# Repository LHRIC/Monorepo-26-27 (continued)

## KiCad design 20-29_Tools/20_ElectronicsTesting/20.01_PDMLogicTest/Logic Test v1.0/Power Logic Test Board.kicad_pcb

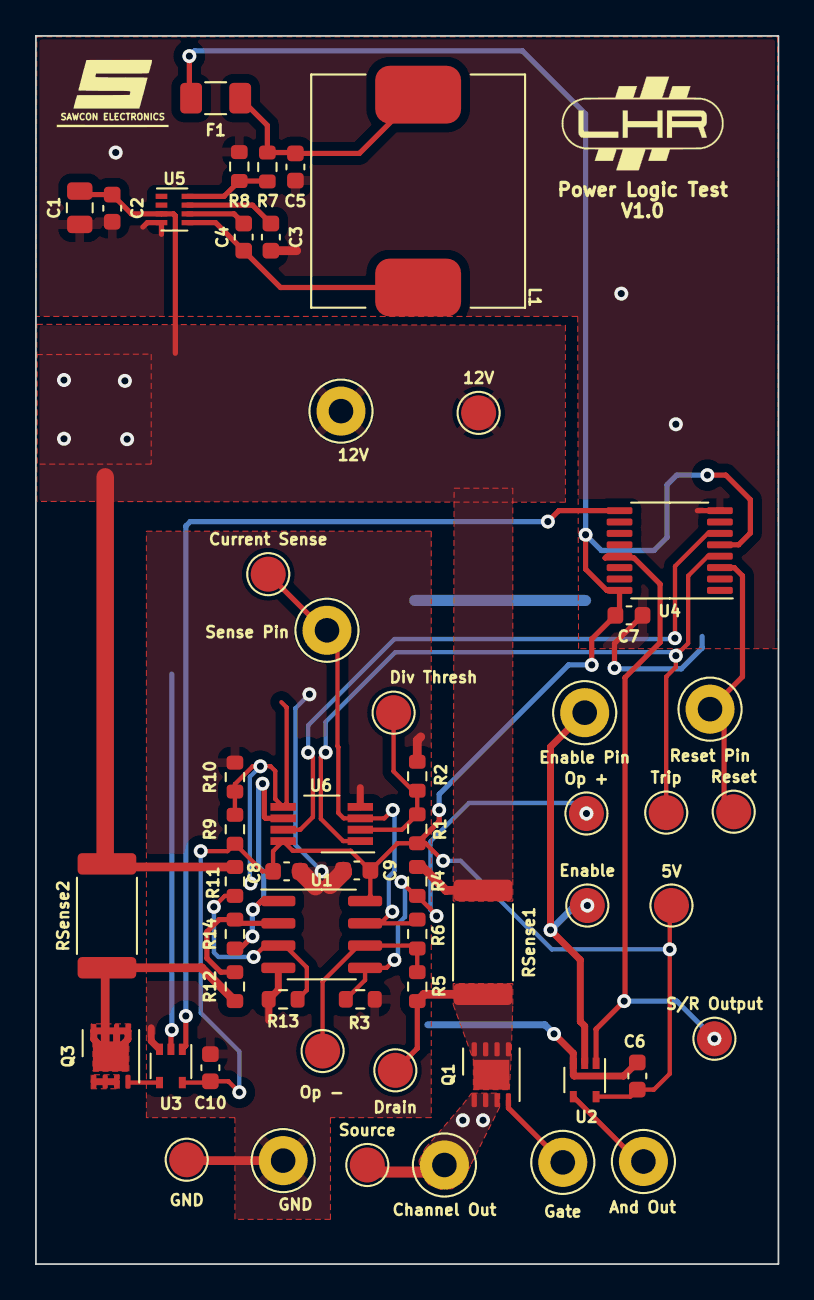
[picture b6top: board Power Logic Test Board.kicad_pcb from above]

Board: 2 copper layers, 42.3 x 70.0 mm, 57 parts (0 on the bottom side), 29 nets.

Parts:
5V, 12V: TP; TestPoint_Pad_D2.0mm
12V#2: TestPoint; TestPoint_Loop_D3.50mm_Drill1.4mm_Beaded
And Out: TestPoint; TestPoint_Loop_D3.50mm_Drill1.4mm_Beaded
C1: 10uF; C_0805_2012Metric
C2, C4: 0.1uF; C_0603_1608Metric
C3: 33nF; C_0603_1608Metric
C5: 47uF; C_0603_1608Metric
C6, C7, C8, C9, C10: C_Small; C_0603_1608Metric
Channel Out: TestPoint; TestPoint_Loop_D3.50mm_Drill1.4mm_Beaded
Current Sense: TestPoint; TestPoint_Pad_D2.0mm
Div Thresh: TestPoint; TestPoint_Pad_D2.0mm
Drain: TestPoint; TestPoint_Pad_D2.0mm
Enable: TestPoint; TestPoint_Pad_D2.0mm
Enable Pin: TestPoint; TestPoint_Loop_D3.50mm_Drill1.4mm_Beaded
F1: 750mA; Fuse_1206_3216Metric
GND: TestPoint; TestPoint_Loop_D3.50mm_Drill1.4mm_Beaded
GND#2: TestPoint; TestPoint_Pad_D2.0mm
Gate: TestPoint; TestPoint_Loop_D3.50mm_Drill1.4mm_Beaded
L1: 5.6uH; HCMA1305-5R6-R
Op +: TestPoint; TestPoint_Pad_D2.0mm
Op -: TestPoint; TestPoint_Pad_D2.0mm
Q1, Q3: NMOS; DFN-8-1EP_3x3mm_P0.65mm_EP1.7x2.05mm
R1, R2, R3, R4, R5, R6, R9, R10, R11, R12, R13, R14: R_Small; R_0603_1608Metric
R7: 52.3k; R_0603_1608Metric
R8: 10k; R_0603_1608Metric
RSense1, RSense2: R_Small; R_2512_6332Metric
Reset: TestPoint; TestPoint_Pad_D2.0mm
Reset Pin: TestPoint; TestPoint_Loop_D3.50mm_Drill1.4mm_Beaded
S/R Output: TestPoint; TestPoint_Pad_D2.0mm
Sense Pin: TestPoint; TestPoint_Loop_D3.50mm_Drill1.4mm_Beaded
Source: TestPoint; TestPoint_Pad_D2.0mm
Trip: TestPoint; TestPoint_Pad_D2.0mm
U1: Opamp_Dual; SOIC-8_3.9x4.9mm_P1.27mm
U2, U3: 74AHC1G08; SOT-353_SC-70-5
U4: CD4044B; TSSOP-16_4.4x5mm_P0.65mm
U5: TPS62933; SOT-583
U6: TLV7012DGKR; VSSOP-8_3.0x3.0mm_P0.65mm

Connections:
+5V: 5V.1, C6.1, C7.1, C8.1, C9.1, C10.1, F1.2, R1.1, R9.1, U1.8 (V+), U2.5 (VCC), U3.5 (VCC), U4.5 (Enable), U4.16 (V+), U6.8 (V+)
+12V: 12V.1, 12V#2.1, C1.1, C2.1, R4.1, R11.1, RSense1.1, RSense2.1, U5.3 (VIN)
/Current Sense: R14.1, U1.1, U6.6 (-)
/Drain: Drain.1, Q1.5 (D), Q1.6 (D), Q1.7 (D), Q1.8 (D), Q1.9 (D), R5.1, RSense1.2
/Fault: U3.1, U4.9 (Q)
/Gate: Gate.1, Q1.4 (G)
/Load+: Q3.1 (S), Q3.2 (S), Q3.3 (S)
/Source: Channel Out.1, Q1.1 (S), Q1.2 (S), Q1.3 (S), Source.1
GND: C1.2, C2.2, C3.2, C5.2, C6.2, C7.2, C8.2, C9.2, C10.2, GND.1, GND#2.1, R2.2, R3.2, R8.2, R10.2, R13.2, U1.4 (V-), U2.3 (GND), U3.3 (GND), U4.8 (V-), U5.4 (GND), U6.4 (V-)
unnamed: C5.1, F1.1, L1.2, R7.1
unnamed: Q3.5 (D), Q3.6 (D), Q3.7 (D), Q3.8 (D), Q3.9 (D), R12.1, RSense2.2
unnamed: Q3.4 (G), U3.4
unnamed: Enable.1, Enable Pin.1, U2.2
unnamed: And Out.1, U2.4
unnamed: R11.2, R13.1, U1.3 (+)
unnamed: R12.2, R14.2, U1.2 (-)
unnamed: Op +.1, R3.1, R4.2, U1.5 (+)
unnamed: Op -.1, R5.2, R6.1, U1.6 (-)
unnamed: S/R Output.1, U2.1, U4.13 (Q)
unnamed: Trip.1, U4.4 (R), U6.1
unnamed: Reset.1, Reset Pin.1, U4.3 (S)
unnamed: U4.6 (R), U6.7
unnamed: C4.1, U5.6 (BST)
unnamed: R7.2, R8.1, U5.8 (FB)
unnamed: C3.1, U5.7 (SS)
unnamed: C4.2, L1.1, U5.5 (SW)
unnamed: Current Sense.1, R6.2, Sense Pin.1, U1.7, U6.3 (+)
unnamed: Div Thresh.1, R1.2, R2.1, U6.2 (-)
unnamed: R9.2, R10.1, U6.5 (+)

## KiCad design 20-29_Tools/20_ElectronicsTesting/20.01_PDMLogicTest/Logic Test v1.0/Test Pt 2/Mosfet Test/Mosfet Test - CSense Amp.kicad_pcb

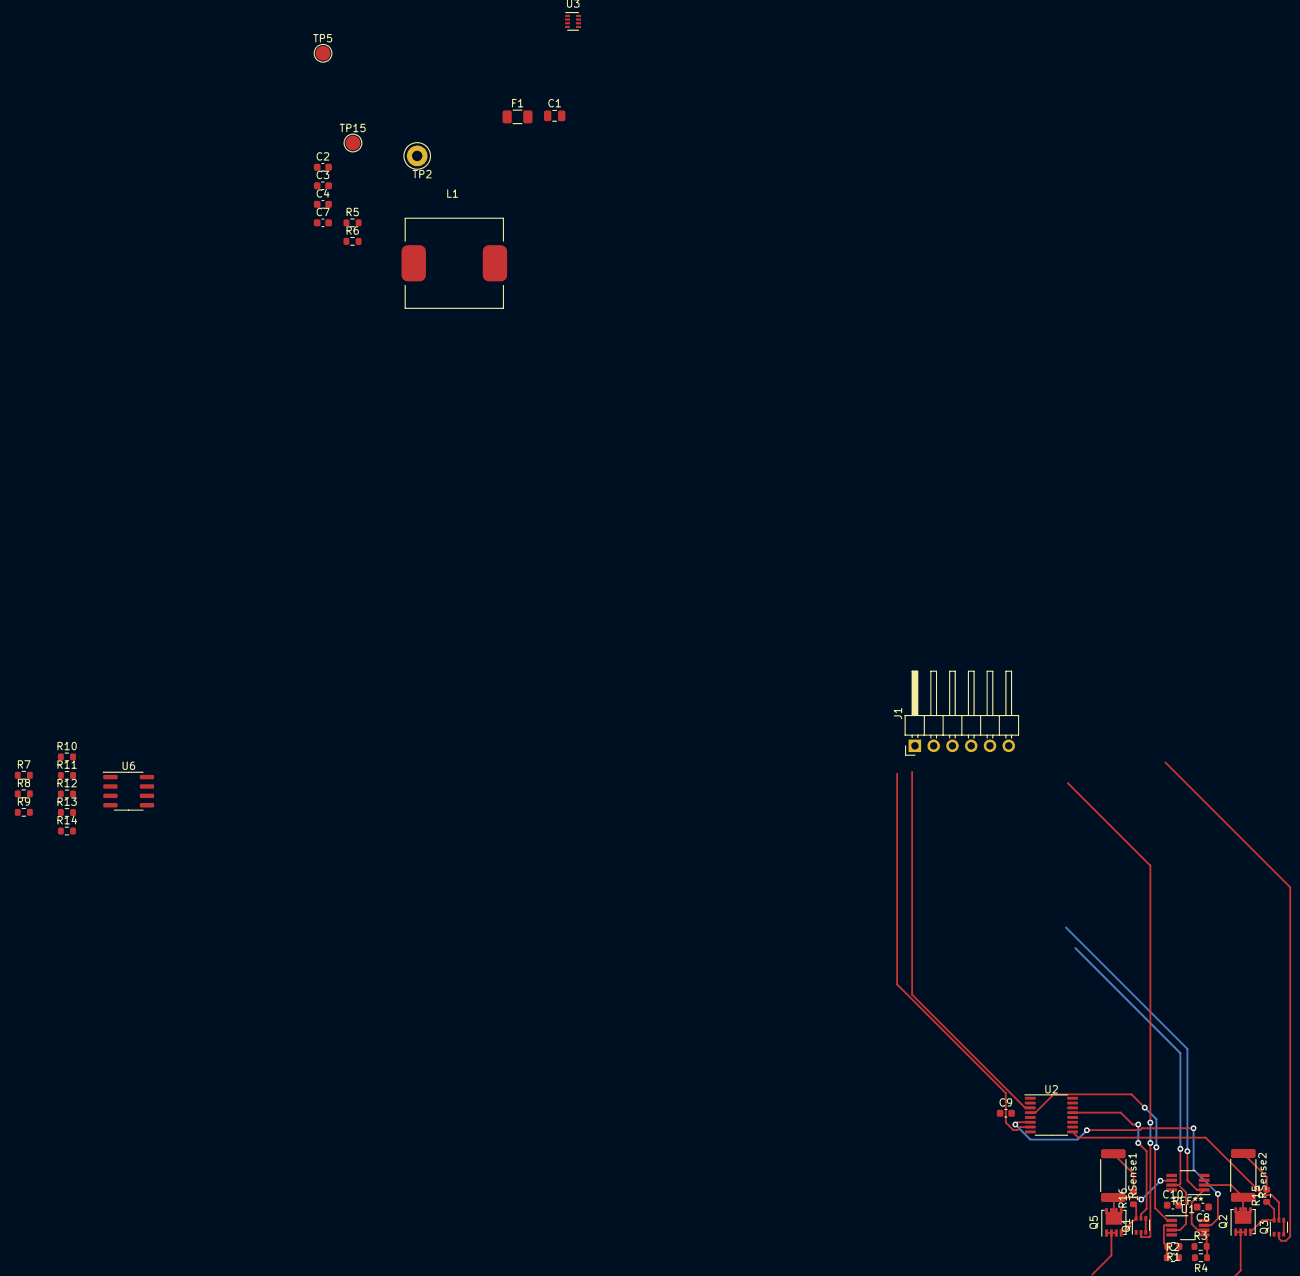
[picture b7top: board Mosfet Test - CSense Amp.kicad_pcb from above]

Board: 2 copper layers, 40 parts (0 on the bottom side), 32 nets.

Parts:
C1: 10uF; C_0805_2012Metric
C2, C4: 0.1uF; C_0603_1608Metric
C3: 33nF; C_0603_1608Metric
C7: 47uF; C_0603_1608Metric
C8, C9, C10: C_Small; C_0603_1608Metric
F1: 750mA; Fuse_1206_3216Metric
J1: Conn_01x06_Pin; PinHeader_1x06_P2.54mm_Horizontal
L1: 5.6uH; HCMA1305-5R6-R
Q1, Q3: DMN63D8LDW; SOT-363_SC-70-6
Q2, Q5: SiS443DN; Vishay_PowerPAK_1212-8_Single
R1, R2, R3, R4, R7, R8, R9, R10, R11, R12, R13, R14: R_Small; R_0603_1608Metric
R5: 52.3k; R_0603_1608Metric
R6: 10k; R_0603_1608Metric
R15, R16: 100k; R_0603_1608Metric
RSense1, RSense2: R_Small; R_2512_6332Metric
TP2: TestPoint; TestPoint_Loop_D3.50mm_Drill1.4mm_Beaded
TP5, TP15: TP; TestPoint_Pad_D2.0mm
U1: TLV7012DGKR; VSSOP-8_3.0x3.0mm_P0.65mm
U2: CD4044B; TSSOP-16_4.4x5mm_P0.65mm
U3: TPS62933; SOT-583
U6: Opamp_Dual; SOIC-8_3.9x4.9mm_P1.27mm

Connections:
+5V: C8.1, C9.1, C10.1, F1.2, R1.1, R3.1, TP15.1, U1.8 (V+), U2.5 (Enable), U2.16 (V+), U6.8 (V+)
+12V: C1.1, C2.1, R7.1, R9.1, R15.2, R16.2, RSense1.1, RSense2.1, TP2.1, TP5.1, U3.3 (VIN)
/Drain: Q5.5 (D), R8.1, RSense1.2
/Fault: Q3.5 (G), U2.9 (Q)
/Load+: Q2.1 (S), Q2.2 (S), Q2.3 (S)
/Source: Q5.1 (S), Q5.2 (S), Q5.3 (S)
CS1: J1.3, R12.2, U1.3 (+), U6.7
CS2: J1.6, R14.1, U1.6 (-), U6.1
EN1: J1.2, Q1.2 (G)
EN2: J1.5, Q3.2 (G)
GND: C1.2, C2.2, C3.2, C7.2, C8.2, C9.2, C10.2, Q1.1 (S), Q3.1 (S), R2.2, R4.2, R6.2, R11.2, R13.2, U1.4 (V-), U2.8 (V-), U3.4 (GND), U6.4 (V-)
unnamed: C7.1, F1.1, L1.2, R5.1
unnamed: Q1.6 (D), Q5.4 (G), R16.1
unnamed: Q1.5 (G), U2.13 (Q)
unnamed: Q1.3 (D), Q1.4 (S)
unnamed: Q2.5 (D), R10.1, RSense2.2
unnamed: Q2.4 (G), Q3.6 (D), R15.1
unnamed: Q3.3 (D), Q3.4 (S)
unnamed: R1.2, R2.1, U1.2 (-)
unnamed: R3.2, R4.1, U1.5 (+)
unnamed: U1.1, U2.4 (R)
unnamed: U1.7, U2.6 (R)
unnamed: C4.1, U3.6 (BST)
unnamed: R5.2, R6.1, U3.8 (FB)
unnamed: C3.1, U3.7 (SS)
unnamed: C4.2, L1.1, U3.5 (SW)
unnamed: R9.2, R13.1, U6.3 (+)
unnamed: R10.2, R14.2, U6.2 (-)
unnamed: R7.2, R11.1, U6.5 (+)
unnamed: R8.2, R12.1, U6.6 (-)
Reset1: J1.1, U2.3 (S)
Reset2: J1.4, U2.7 (S)
